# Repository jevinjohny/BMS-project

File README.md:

# 🔋 Battery Management System for Low Voltage Low Power Domestic Equipment

🎓 **B.Tech Final Year Project**  
🏫 Government Engineering College, Barton Hill  
👤 **Author**: Jevin Johny V  

---

## 📘 Overview

This project presents a compact, stackable **Battery Management System (BMS)** designed for small domestic devices like robotic vacuum cleaners. It incorporates passive cell balancing, safety protections, and real-time SoC estimation.

---

## 🛠️ Tools & Technologies

- **Microcontroller**: Texas Instruments TMS320F28379D  
- **PCB Design**: KiCad (schematic + 2-layer layout + Gerber)  
- **Simulation**: MATLAB Simulink Embedded Coder  
- **Programming**: Embedded C, ADC configuration, interrupt handling  
- **IC Used**: BQ77915 (cell balancing, protection)

---

## 🧑‍💻 My Contributions

- ✅ Complete microcontroller development (ADC, ISR, SoC logic)
- ✅ Designed custom 2-layer PCB using KiCad with Gerber generation
- ✅ Simulated SoC estimation algorithm in MATLAB
- ✅ Tested protection features and built prototype on hardware

---

## 📂 Project Structure

| Folder | Description |
|--------|-------------|
| `kicad` | Schematic, layout, and Gerber files for the PCB |
| `screenshots` | Photos of hardware, layout, schematic, and testing |
| `README.md` | Project summary |
| `LICENSE` | MIT License (recommended for open source use) |

---

## 🖼️ Preview
### 🔌 Schematic

### 🔌 PCB Design

### 🧪 Testing

### 📊 MATLAB Simulation

---

## 💡 Features

- Passive balancing with BQ77915 + external FETs
- 6S Li-ion configuration (4.2V max per cell)
- Overvoltage, undervoltage, and thermal protection
- SoC and SoH estimation using modified Coulomb Counting
- Stackable design for scalability

---

## 📬 Contact

I’m actively seeking entry-level opportunities in **Embedded Systems**, **PCB Design**, or **Electronics Engineering**.  
Let’s connect on [LinkedIn](https://www.linkedin.com/in/jevinjohny) (replace with your link).

---

## 📄 License

This project is open-sourced under the MIT License – feel free to explore, adapt, or build upon it.

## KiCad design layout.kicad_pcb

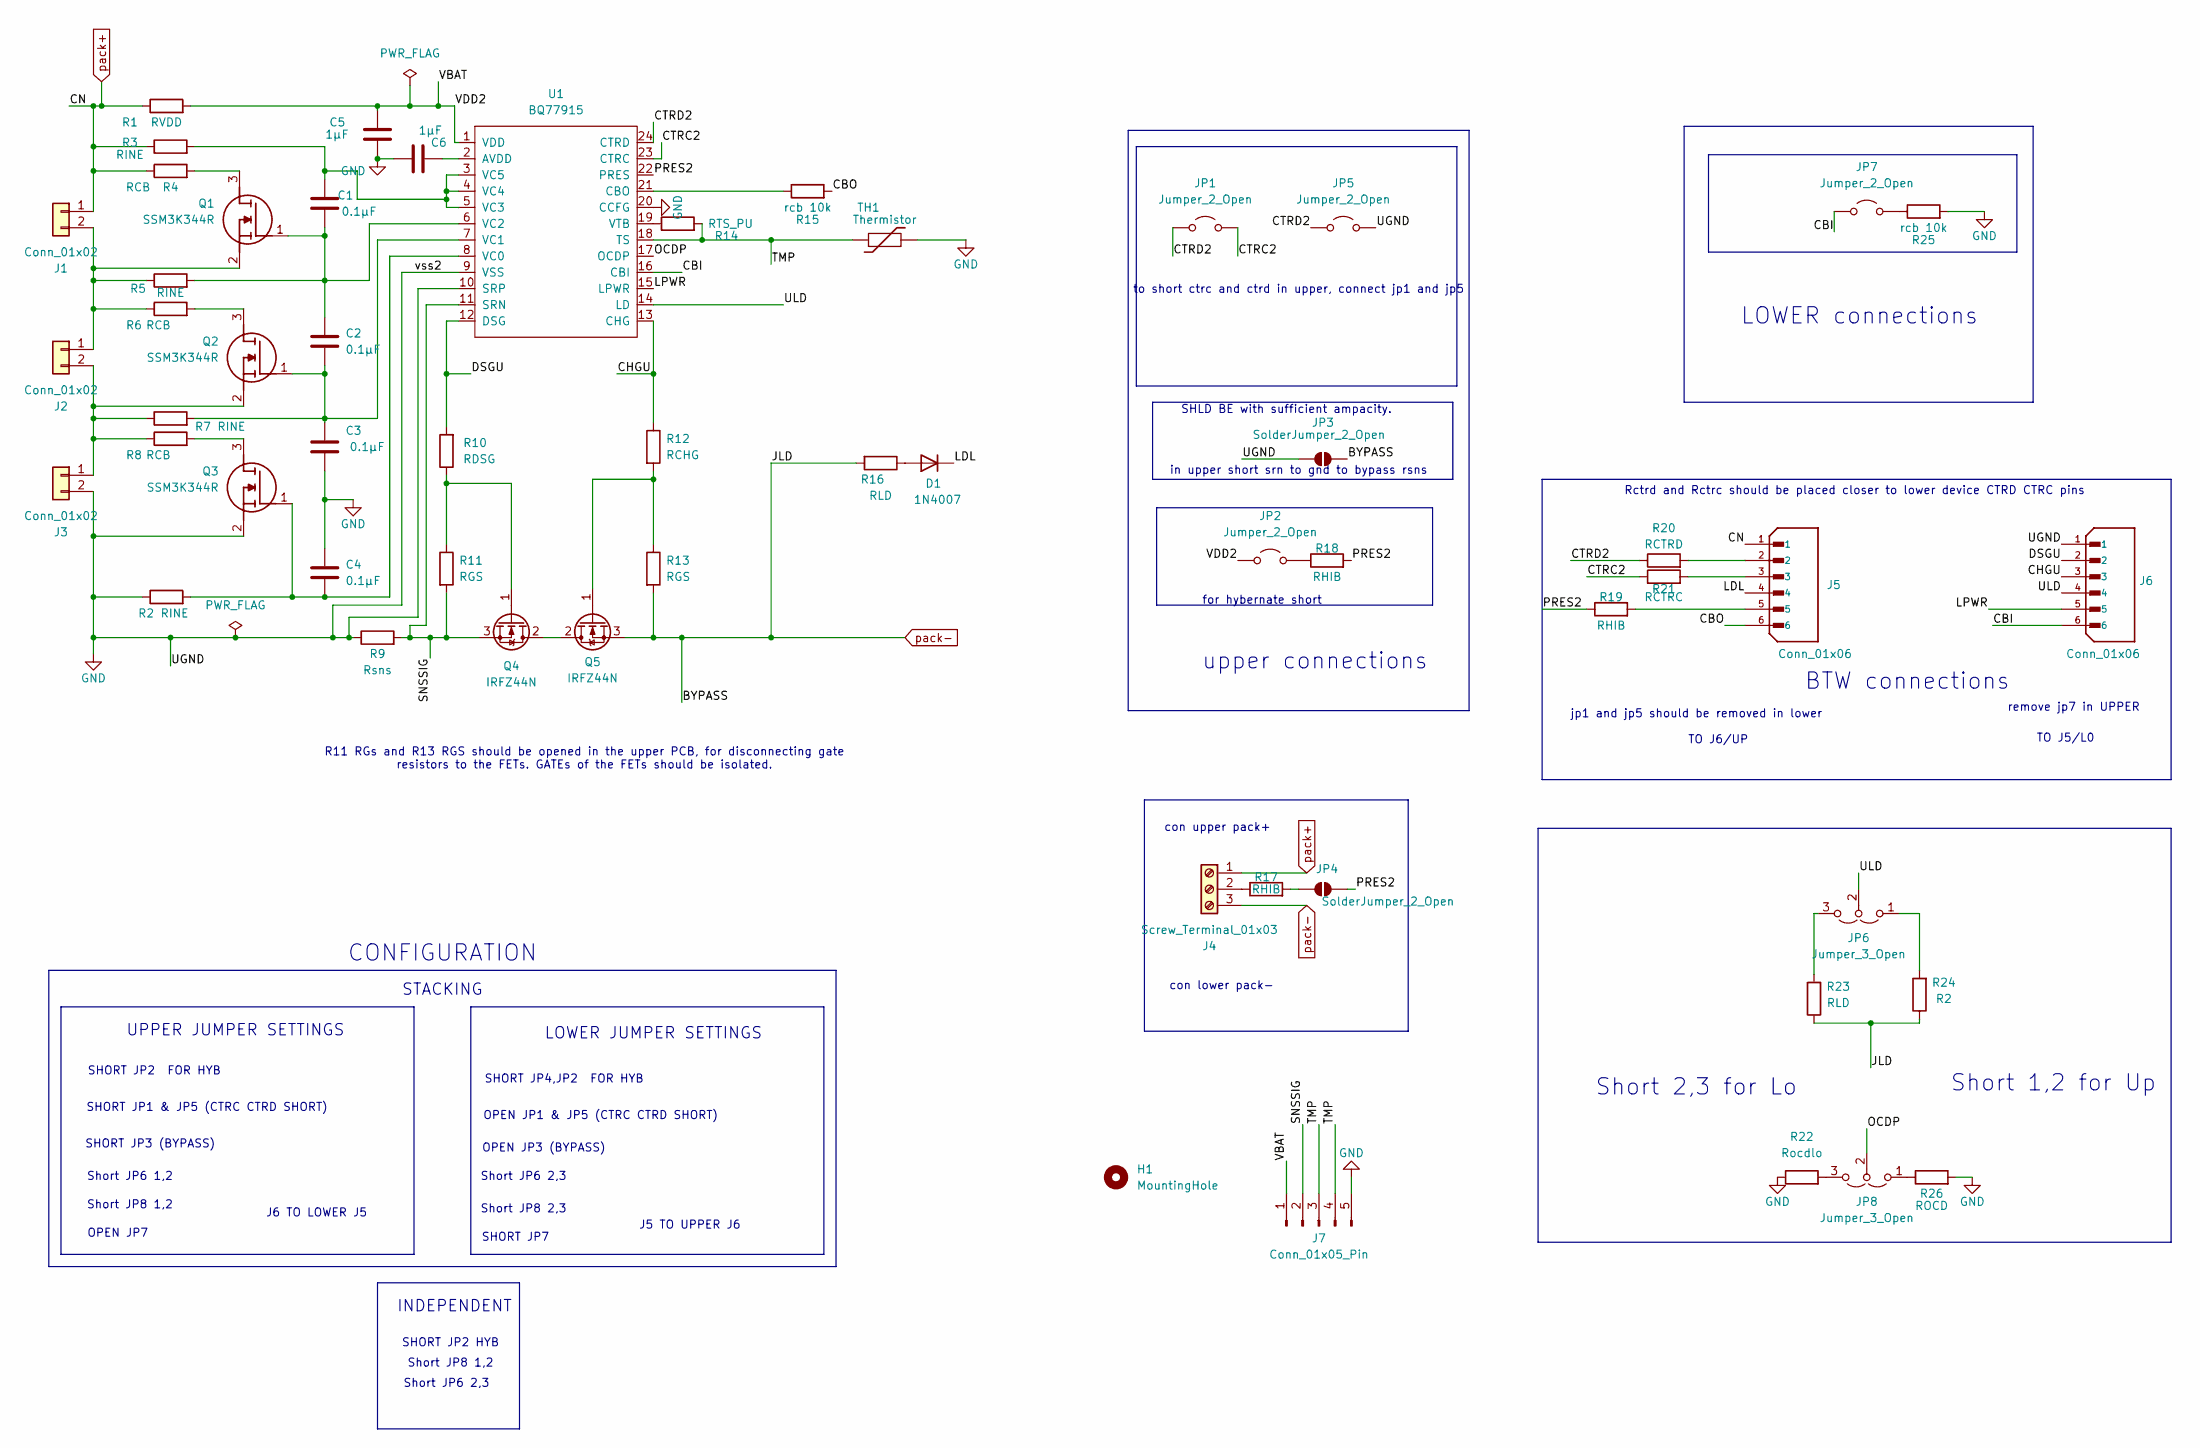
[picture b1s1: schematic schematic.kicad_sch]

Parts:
C1, C2, C3, C4: 0.1µF; CAP_CL05_SAM; Manufacturer_Part_Number CL05B104KP5NNNC
C5, C6: 1µF; CAP_1005_TDK; Manufacturer_Part_Number GRM033R60J105MEA2D
D1: 1N4007; D_DO-34_SOD68_P2.54mm_Vertical_AnodeUp; Manufacturer_Part_Number 1N4007
H1: MountingHole; MountingHole_2.1mm
J1, J2, J3: Conn_01x02; JST_EH_B2B-EH-A_1x02_P2.50mm_Vertical; Manufacturer_Part_Number B2B-EH-A
J4: Screw_Terminal_01x03
J5, J6: Conn_01x06; JST_PH_B6B-PH-K_1x06_P2.00mm_Vertical; PARTREV 7/4/21
J7: Conn_01x05_Pin; PinHeader_1x05_P2.54mm_Vertical
JP1, JP2, JP5, JP7: Jumper_2_Open; PinHeader_1x02_P2.54mm_Vertical; Manufacturer_Part_Number PH1-02-UA
JP3, JP4: SolderJumper_2_Open; SolderJumper-2_P1.3mm_Open_RoundedPad1.0x1.5mm
JP6, JP8: Jumper_3_Open; PinHeader_1x03_P2.54mm_Vertical; Manufacturer_Part_Number 61300311121
Q1, Q2, Q3: SSM3K344R; SOT-23F_TOS; Manufacturer_Part_Number SSM3K344R
Q4, Q5: IRFZ44N; TO-220-3_Horizontal_TabDown
R1: RVDD; RC0402N_YAG; Manufacturer_Part_Number RC0402JR-071KL
R2, R3, R5, R7: RINE; RC0402N_YAG; Manufacturer_Part_Number RC0402JR-071KL
R4, R6, R8: RCB; RES_RMCF2512_STP; Manufacturer_Part_Number RMCF2512JT18R0
R9: Rsns; RES_1632_SUS; Manufacturer_Part_Number RL1632R-R056-F
R10: RDSG; RC0805N_PAN; Manufacturer_Part_Number ERJ-P06J472V
R11, R13: RGS; RESC1005X40N; Manufacturer_Part_Number CRGCQ0402J1M0
R12: RCHG; RES_ERJP06J102V; Manufacturer_Part_Number ERJ_P06J102V
R14: RTS_PU; RC0402N_YAG; Manufacturer_Part_Number RC0402JR-0710KL
R15, R25: rcb 10k; RC0402N_YAG; Manufacturer_Part_Number RC0402JR-0710KL
R16, R23: RLD; RES_CRGCQ0402J10M_TEC-L; Manufacturer_Part_Number CRGCQ0402J10M
R17, R18, R19: RHIB; RC0402N_YAG; Manufacturer_Part_Number RC0402JR-0710KL
R20: RCTRD; RESC1005X40N; Manufacturer_Part_Number CRGCQ0402J1M0
R21: RCTRC; RESC1005X40N; Manufacturer_Part_Number CRGCQ0402J1M0
R22: Rocdlo; RC0603N_YAG; Manufacturer_Part_Number RC0603FR-07487KL
R24: R2; RES_CRGCQ0402J10M_TEC-L; Manufacturer_Part_Number CRGCQ0402J10M
R26: ROCD; RESC1005X35N; Manufacturer_Part_Number CRCW040210M0FKEDC
TH1: Thermistor; THERM_NTCG103JF103FT1; Manufacturer_Part_Number NTCG103JF103FT1
U1: BQ77915; SOP65P640X120-24N

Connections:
/CBI: J6.6, JP7.1 (A), U1.16 (CBI)
/CBO: J5.6, R15.2
/CHGU: J6.3, R12.1, U1.13 (CHG)
/CTRC2: JP1.2 (B), R21.1, U1.23 (CTRC)
/CTRD2: JP1.1 (A), JP5.1 (A), R20.1, U1.24 (CTRD)
/DSGU: J6.2, R10.2, U1.12 (DSG)
/LDL: D1.1 (K), J5.4
/LPWR: J6.5, U1.15 (LPWR)
/OCDP: JP8.2 (C), U1.17 (OCDP)
/PRES2: JP4.2 (B), R18.2, R19.1, U1.22 (PRES)
/SNSSIG: J7.2, Q4.3 (S), R9.2, R11.2, U1.11 (SRN)
/TMP: J7.3, J7.4, R14.2, TH1.1, U1.18 (TS)
/ULD: J6.4, JP6.2 (C), U1.14 (LD)
/VBAT: C5.1, J7.1, JP2.1 (A), R1.2, U1.1 (VDD)
GND: C3.2, C4.1, C5.2, C6.2, J3.2, J6.1, J7.5, JP3.1 (A), JP5.2 (B), Q3.2 (S), R2.1, R9.1, R22.1, R25.2, R26.2, TH1.2, U1.9 (VSS), U1.10 (SRP), U1.20 (CCFG)
unnamed: D1.2 (A), R16.1
unnamed: J1.2, J2.1, Q1.2 (S), R5.1, R6.1
unnamed: J2.2, J3.1, Q2.2 (S), R7.1, R8.1
unnamed: J4.2, R17.1
unnamed: J5.2, R20.2
unnamed: J5.3, R21.2
unnamed: J5.5, R19.2
unnamed: JP2.2 (B), R18.1
unnamed: JP4.1 (A), R17.2
unnamed: JP6.1 (A), R24.2
unnamed: JP6.3 (B), R23.2
unnamed: JP7.2 (B), R25.1
unnamed: JP8.1 (A), R26.1
unnamed: JP8.3 (B), R22.2
unnamed: Q1.3 (D), R4.2
unnamed: C1.2, C2.1, Q1.1 (G), R5.2, U1.6 (VC2)
unnamed: Q2.3 (D), R6.2
unnamed: C2.2, C3.1, Q2.1 (G), R7.2, U1.7 (VC1)
unnamed: Q3.3 (D), R8.2
unnamed: C4.2, Q3.1 (G), R2.2, U1.8 (VC0)
unnamed: Q4.2 (D), Q5.2 (D)
unnamed: Q4.1 (G), R10.1, R11.1
unnamed: Q5.1 (G), R12.2, R13.1
unnamed: C6.1, U1.2 (AVDD)
unnamed: R15.1, U1.21 (CBO)
unnamed: C1.1, R3.2, U1.3 (VC5), U1.4 (VC4), U1.5 (VC3)
unnamed: R14.1, U1.19 (VTB)
pack+: J1.1, J4.1, J5.1, R1.1, R3.1, R4.1
pack-: J4.3, JP3.2 (B), Q5.3 (S), R13.2, R16.2, R23.1, R24.1

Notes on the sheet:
Short JP8 2,3
Short 2,3 for Lo
R11 RGs and R13 RGS should be opened in the upper PCB, for disconnecting gate resistors to the FETs. GATEs of the FETs should be isolated.
OPEN JP7
Short JP6 1,2
con lower pack-
OPEN JP1 & JP5 (CTRC CTRD SHORT)
LOWER connections
in upper short srn to gnd to bypass rsns
SHLD BE with sufficient ampacity.
SHORT JP2 HYB
STACKING
SHORT JP3 (BYPASS)
INDEPENDENT
con upper pack+
Short 1,2 for Up
J6 TO LOWER J5
SHORT JP2 FOR HYB
Short JP6 2,3
SHORT JP1 & JP5 (CTRC CTRD SHORT)
upper connections
SHORT JP4,JP2 FOR HYB
for hybernate short
LOWER JUMPER SETTINGS
Short JP8 1,2
to short ctrc and ctrd in upper, connect jp1 and jp5
OPEN JP3 (BYPASS)
TO J5/L0
SHORT JP7
BTW connections
jp1 and jp5 should be removed in lower
UPPER JUMPER SETTINGS
TO J6/UP
J5 TO UPPER J6
CONFIGURATION
remove jp7 in UPPER
Rctrd and Rctrc should be placed closer to lower device CTRD CTRC pins

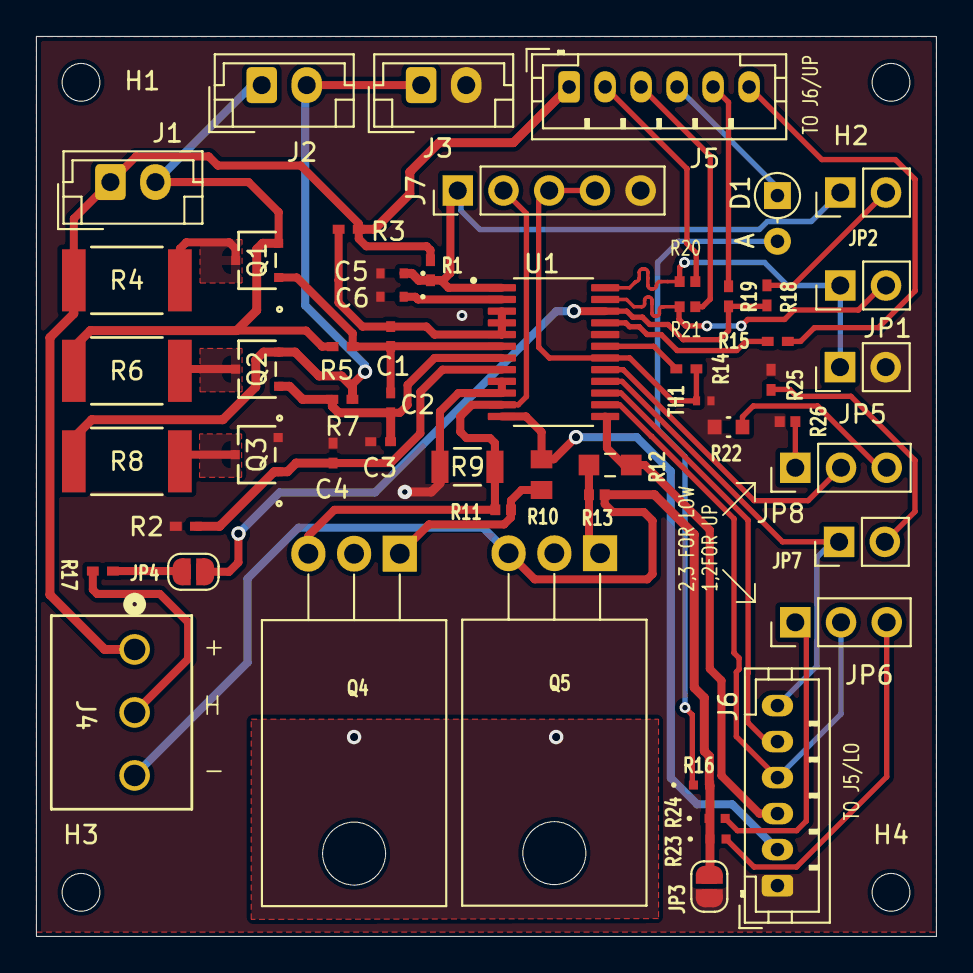
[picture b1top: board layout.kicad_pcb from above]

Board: 2 copper layers, 50.0 x 50.0 mm, 59 parts (0 on the bottom side), 44 nets.

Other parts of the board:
H2, H3, H4: MountingHole; MountingHole_2.1mm

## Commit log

2025-07-10 Create KiCad_PCB
